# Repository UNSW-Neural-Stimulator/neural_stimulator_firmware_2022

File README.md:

# Neural Stimulator Firmware 2022

This is the repository for the Neural Stimulator Firmware team for 2022.

## Contents:

All of the work of the Firmware team for this year is divided up into two folders:
* The `/firmware` folder contains the actual firmware for the project
  * The `NSTIM` project in the `BLE_DAC` workspace contains the actual firmware for the neural stimulator.
* The `/other` folder contains all of the other code created by the team (i.e. weekly tasks)

## Making Changes:

If you wish to make any changes to the repo, please do the following: 
* Make a copy of the repository using `git clone <SSH or HTTPS>`
* Make a new branch for the repo:
  * On **GitHub**: Using the branches, enter your new branch name and click "create"
  * On **Local Terminal**: Enter into your terminal: `git checkout -b <new_branch_name>`
* Checkout your new branch in the terminal by entering `git fetch && git checkout <new_branch_name>`
* Regularly commit your changes by using `git add` and `git commit`
* When you wish to push your local branch changes to your remote branch, use `git push origin <new_branch_name>` 
* When you wish to merge your changes into the `master` branch, visit the branches page and select, "New pull request" [^1]

[^1]: It's not good practice to push anything directly to the `master` branch. By creating pull requests, it allows for somebody else to review your code and also makes it easier to isolate errors (since pull requests often contain multiple commits)

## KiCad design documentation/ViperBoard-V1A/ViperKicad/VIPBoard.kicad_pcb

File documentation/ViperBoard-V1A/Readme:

# Readme

  * Manufacture:
    Contains files sent to JLCPCB for manufacture and assembly. This includes BOM and pick and place position file. Solder mask contains exclusions for parts unable to be sourced from manufacturer.
  * ViperKicad:
    The KiCad 6.0 project. Includes schematic and PCB layout.
  * Documents:
    interactive_pcb.html: Very useful to view where things are on the PCB. Provides interactive inspection of component values and nets.
    VIPBoard-schematic.pdf: Circuit schematic of the stimulator. First sheet contains hierarchy. Following pages contain subcircuits e.g. MCU and current source.
    VIPBoard_3D.step: 3D model of the board and components. 
                      **For reference and graphical illustration ONLY.** 
                      Should not be considered dimensionally accurate as components are not sourced from datasheets.

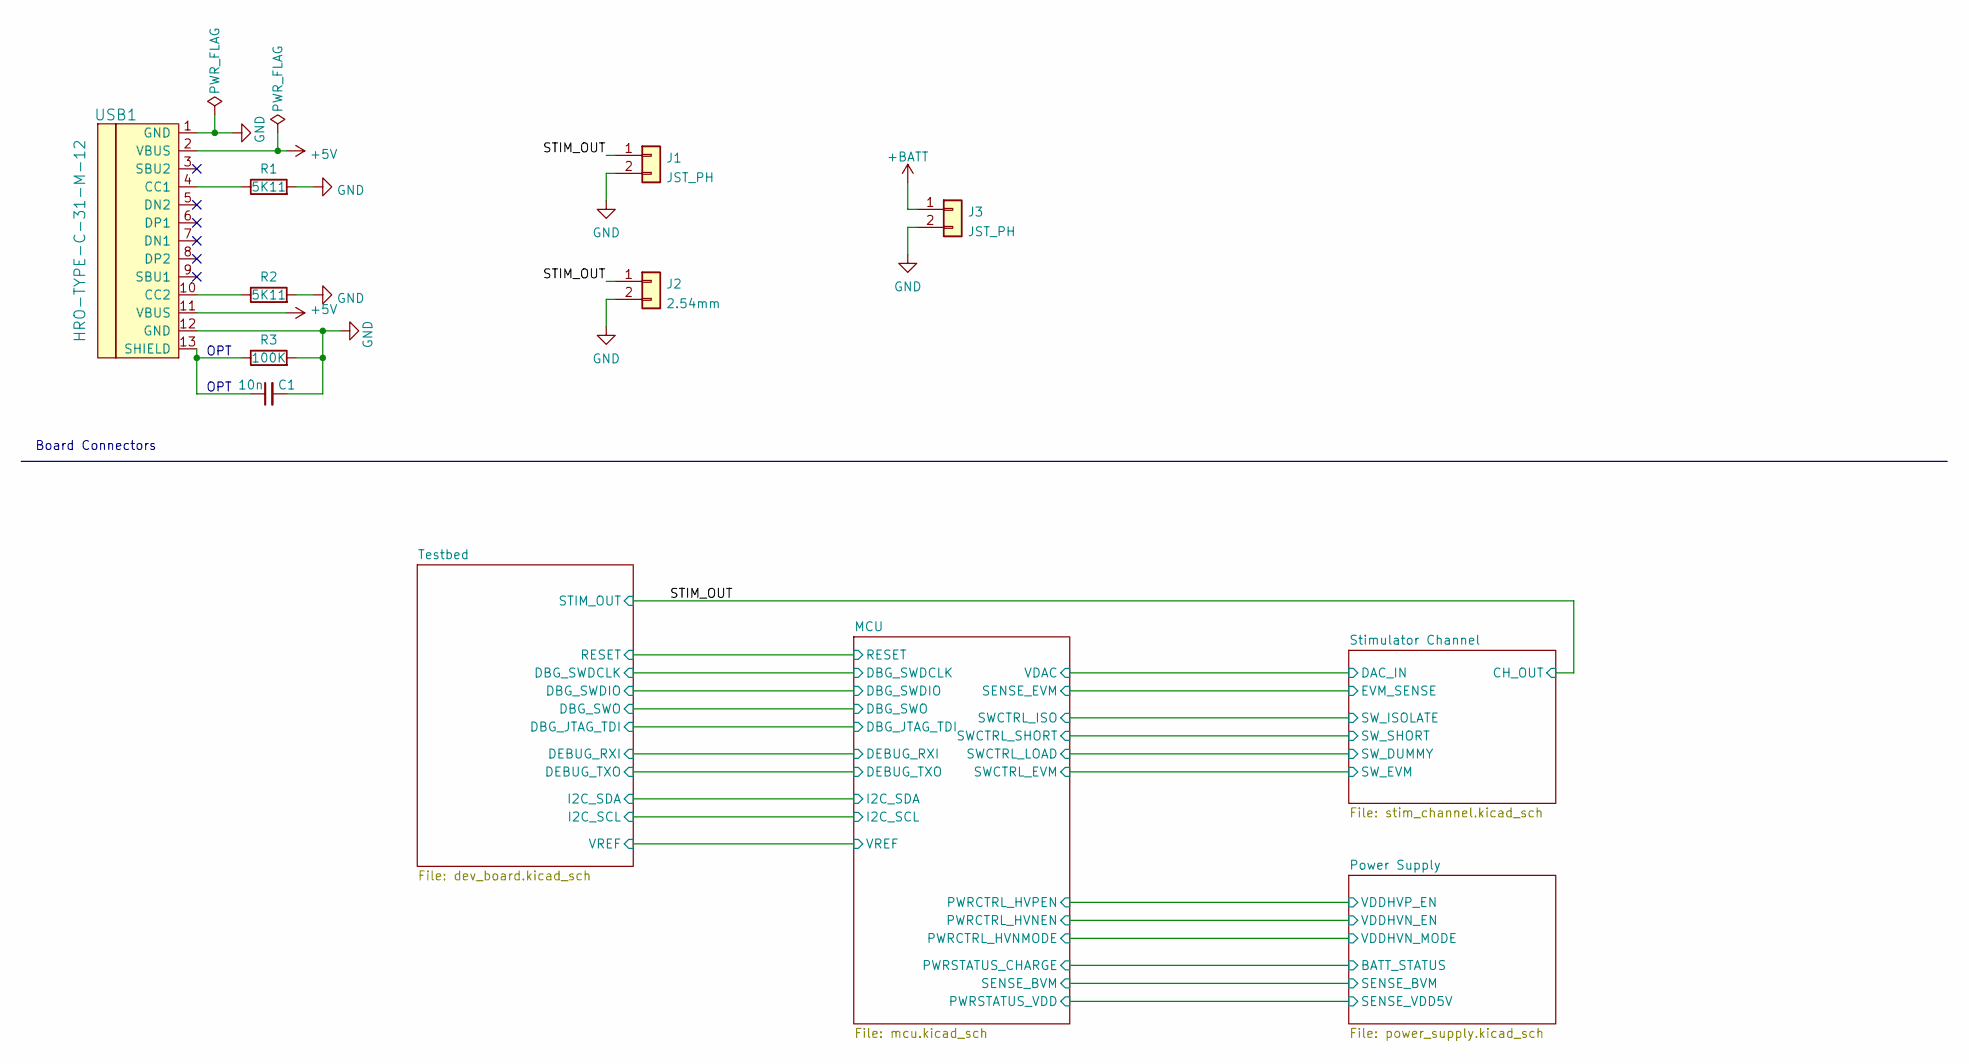
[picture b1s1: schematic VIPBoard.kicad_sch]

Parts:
C1: 10n; C_0402_1005Metric; LCSC C15195
J1, J3: JST_PH; JST_PH_S2B-PH-K_1x02_P2.00mm_Horizontal; LCSC C16965
J2: 2.54mm; PinHeader_1x02_P2.54mm_Vertical
R1, R2: 5K11; R_0402_1005Metric; LCSC C25905
R3: 100K; R_0402_1005Metric; LCSC C25741
USB1: HRO-TYPE-C-31-M-12; HRO-TYPE-C-31-M-12-HandSoldering; LCSC C167321

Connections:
+5V: USB1.2 (VBUS), USB1.11 (VBUS); also elsewhere on the board
+BATT: J3.1; also elsewhere on the board
/STIM_OUT: J1.1, J2.1; also elsewhere on the board
GND: C1.2, J1.2, J2.2, J3.2, R1.2, R2.2, R3.2, USB1.1 (GND), USB1.12 (GND); also elsewhere on the board
unnamed: C1.1, R3.1, USB1.13 (SHIELD)
unnamed: R1.1, USB1.4 (CC1)
unnamed: R2.1, USB1.10 (CC2)

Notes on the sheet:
Board Connectors
OPT

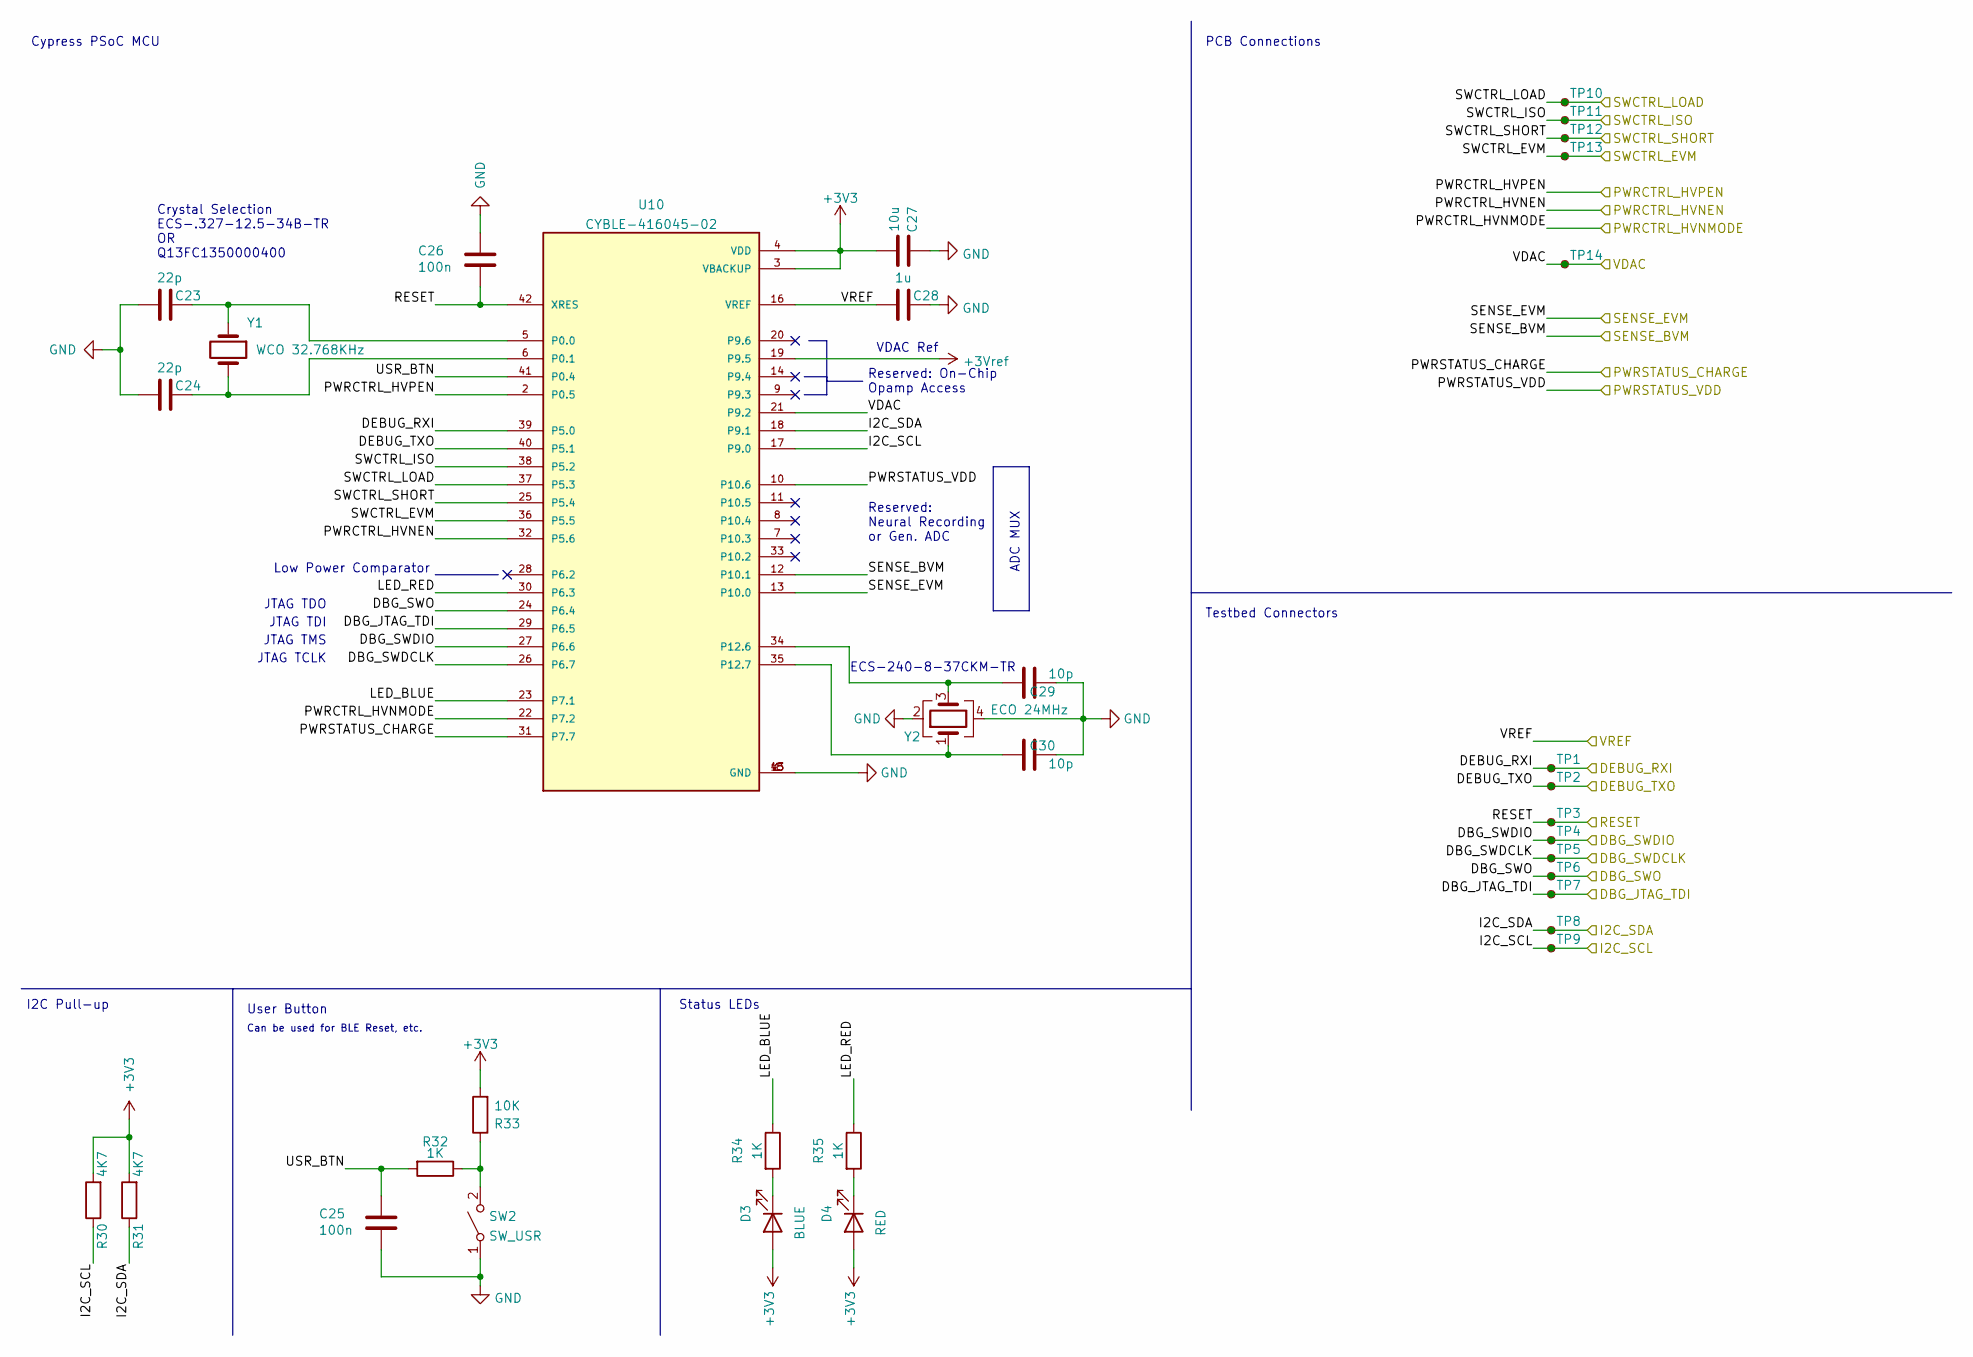
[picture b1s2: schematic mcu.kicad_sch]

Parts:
C23, C24: 22p; C_0402_1005Metric; LCSC C1555
C25, C26: 100n; C_0402_1005Metric; LCSC C307331
C27: 10u; C_0805_2012Metric; LCSC C440198
C28: 1u; C_0805_2012Metric; LCSC C28323
C29, C30: 10p; C_0402_1005Metric; LCSC C32949
D3: BLUE; LED_0603_1608Metric; LCSC C72041
D4: RED; LED_0603_1608Metric; LCSC C2286
R30, R31: 4K7; R_0402_1005Metric; LCSC C25900
R32, R34, R35: 1K; R_0402_1005Metric; LCSC C11702
R33: 10K; R_0402_1005Metric; LCSC C25744
SW2: SW_USR; SW_SPST_TL3342; LCSC C318884
TP1, TP2, TP3, TP4, TP5, TP6, TP7, TP8, TP9, TP10, TP11, TP12, TP13, TP14: TestPoint_Small; TestPoint_Pad_D1.0mm
U10: CYBLE-416045-02; XCVR_CYBLE-416045-02; PARTREV A
Y1: WCO 32.768KHz; Crystal_SMD_3215-2Pin_3.2x1.5mm; LCSC C32346
Y2: ECO 24MHz; Crystal_SMD_2016-4Pin_2.0x1.6mm

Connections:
+3V3: C27.2, D3.2 (A), D4.2 (A), R30.2, R31.2, R33.2, U10.3 (VBACKUP), U10.4 (VDD); also elsewhere on the board
+3Vref: U10.19 (P9.5); also elsewhere on the board
/MCU/DBG_JTAG_TDI: TP7.1, U10.29 (P6.5); also elsewhere on the board
/MCU/DBG_SWDCLK: TP5.1, U10.26 (P6.7); also elsewhere on the board
/MCU/DBG_SWDIO: TP4.1, U10.27 (P6.6); also elsewhere on the board
/MCU/DBG_SWO: TP6.1, U10.24 (P6.4); also elsewhere on the board
/MCU/DEBUG_RXI: TP1.1, U10.39 (P5.0); also elsewhere on the board
/MCU/DEBUG_TXO: TP2.1, U10.40 (P5.1); also elsewhere on the board
/MCU/I2C_SCL: R30.1, TP9.1, U10.17 (P9.0); also elsewhere on the board
/MCU/I2C_SDA: R31.1, TP8.1, U10.18 (P9.1); also elsewhere on the board
/MCU/LED_BLUE: R34.1, U10.23 (P7.1)
/MCU/LED_RED: R35.1, U10.30 (P6.3)
/MCU/PWRCTRL_HVNEN: U10.32 (P5.6); also elsewhere on the board
/MCU/PWRCTRL_HVNMODE: U10.22 (P7.2); also elsewhere on the board
/MCU/PWRCTRL_HVPEN: U10.2 (P0.5); also elsewhere on the board
/MCU/PWRSTATUS_CHARGE: U10.31 (P7.7); also elsewhere on the board
/MCU/PWRSTATUS_VDD: U10.10 (P10.6); also elsewhere on the board
/MCU/RESET: C26.2, TP3.1, U10.42 (XRES); also elsewhere on the board
/MCU/SENSE_BVM: U10.12 (P10.1); also elsewhere on the board
/MCU/SENSE_EVM: U10.13 (P10.0); also elsewhere on the board
/MCU/SWCTRL_EVM: TP13.1, U10.36 (P5.5); also elsewhere on the board
/MCU/SWCTRL_ISO: TP11.1, U10.38 (P5.2); also elsewhere on the board
/MCU/SWCTRL_LOAD: TP10.1, U10.37 (P5.3); also elsewhere on the board
/MCU/SWCTRL_SHORT: TP12.1, U10.25 (P5.4); also elsewhere on the board
/MCU/USR_BTN: C25.1, R32.2, U10.41 (P0.4)
/MCU/VDAC: TP14.1, U10.21 (P9.2); also elsewhere on the board
/MCU/VREF: C28.2, U10.16 (VREF); also elsewhere on the board
GND: C23.2, C24.2, C25.2, C26.1, C27.1, C28.1, C29.2, C30.2, SW2.1 (A), U10.1 (GND), U10.15 (GND), U10.43 (GND), Y2.2, Y2.4; also elsewhere on the board
unnamed: C23.1, U10.5 (P0.0), Y1.1
unnamed: C24.1, U10.6 (P0.1), Y1.2
unnamed: C29.1, U10.34 (P12.6), Y2.3
unnamed: C30.1, U10.35 (P12.7), Y2.1
unnamed: D3.1 (K), R34.2
unnamed: D4.1 (K), R35.2
unnamed: R32.1, R33.1, SW2.2 (B)

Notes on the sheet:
Low Power Comparator
JTAG TCLK
Reserved: On-Chip Opamp Access
Can be used for BLE Reset, etc.
Reserved: Neural Recording or Gen. ADC
Crystal Selection ECS-.327-12.5-34B-TR OR Q13FC1350000400
Testbed Connectors
JTAG TDO
JTAG TMS
ECS-240-8-37CKM-TR
I2C Pull-up
PCB Connections
Cypress PSoC MCU
VDAC Ref
JTAG TDI
ADC MUX
User Button
Status LEDs

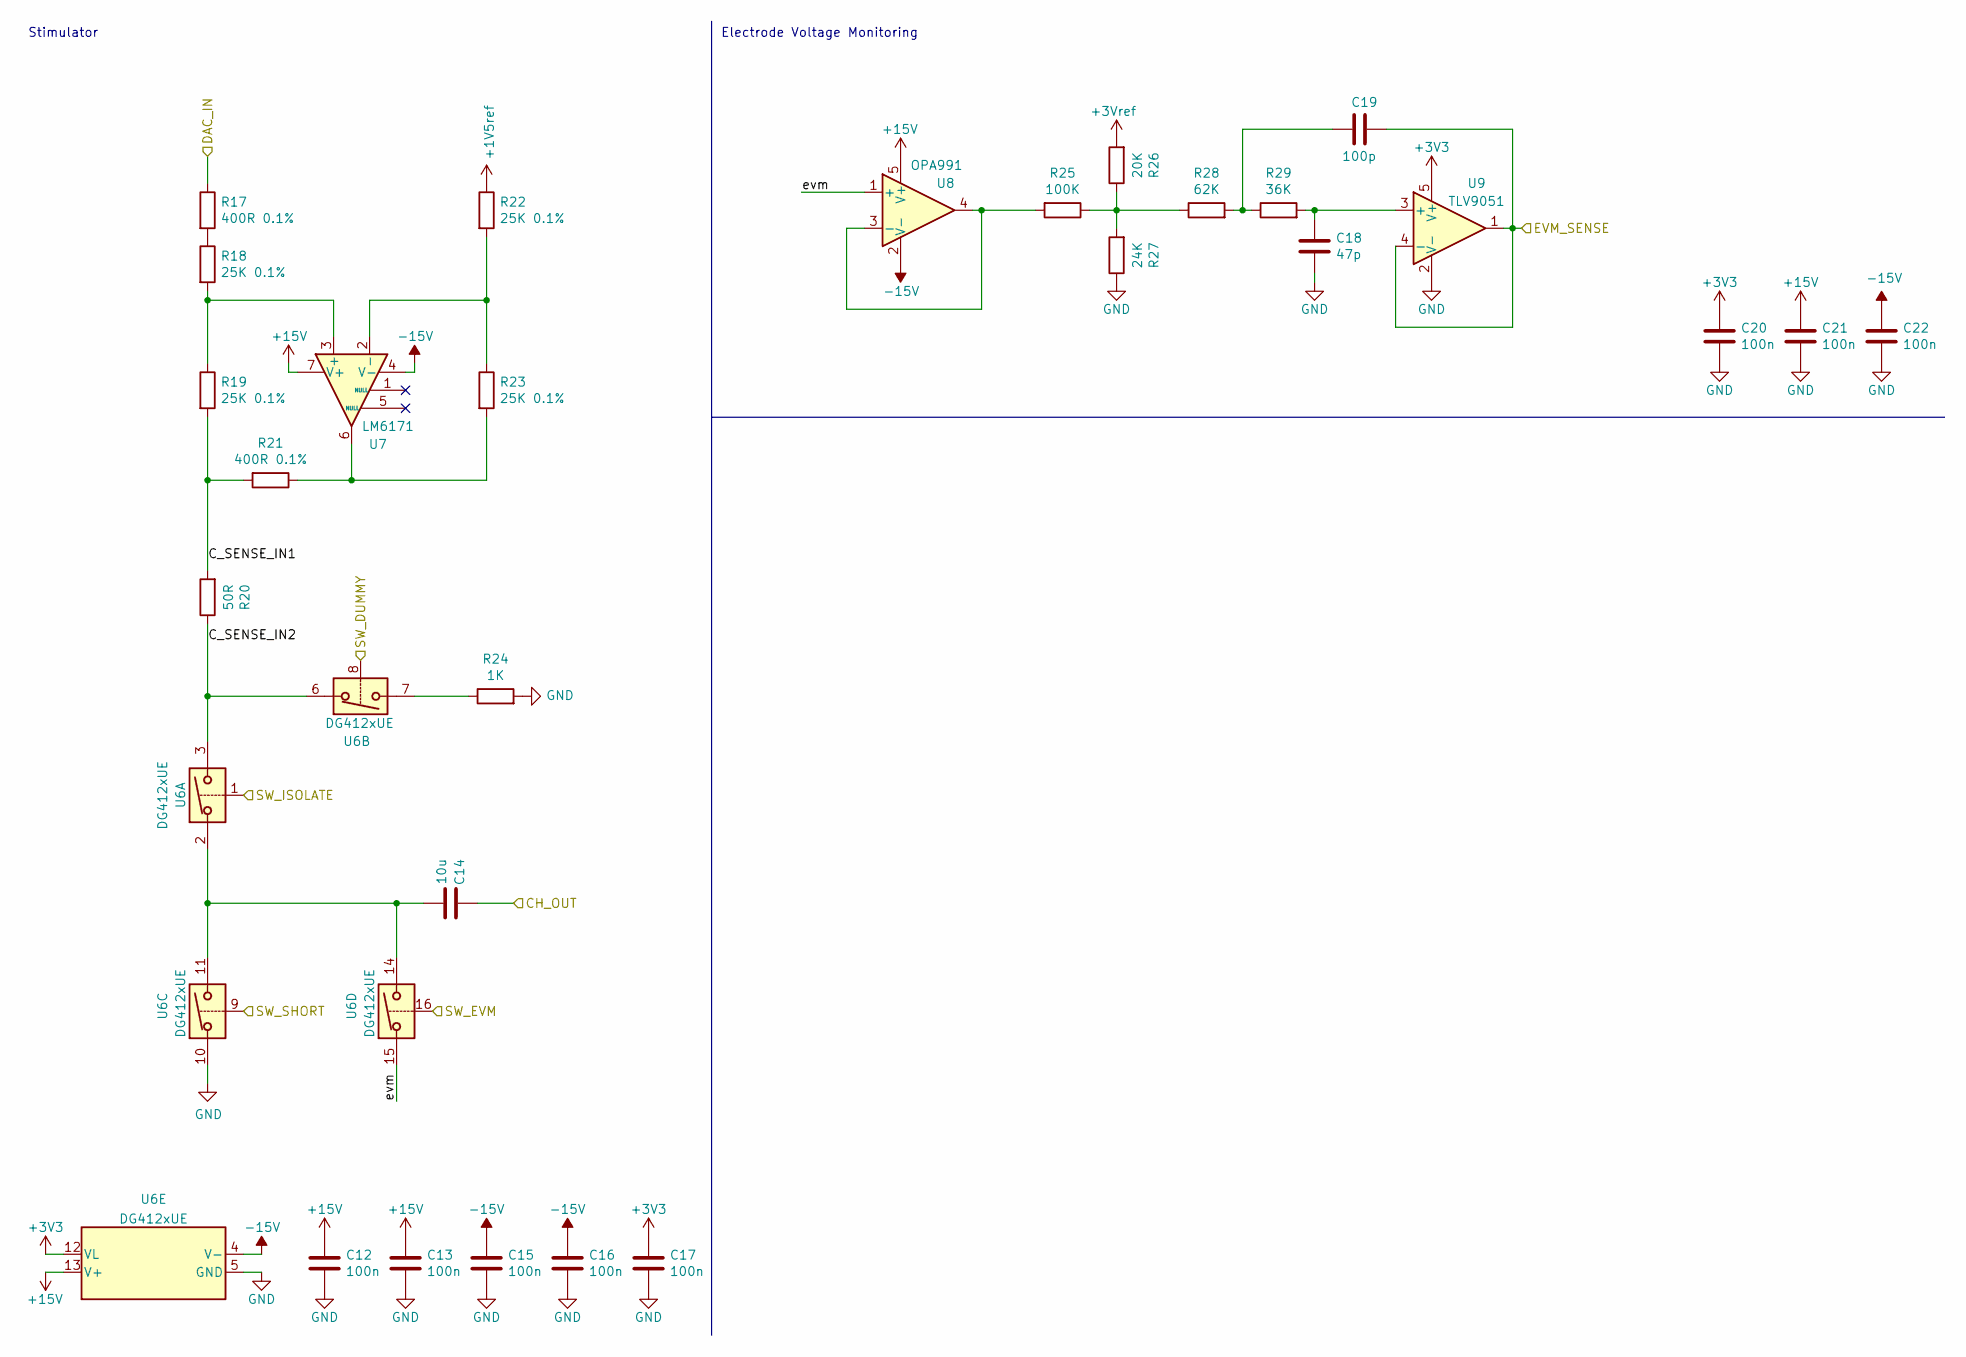
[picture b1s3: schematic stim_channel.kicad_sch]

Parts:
C12, C13, C15, C16, C17, C20, C21, C22: 100n; C_0402_1005Metric; LCSC C307331
C14: 10u; C_0805_2012Metric; LCSC C440198
C18: 47p; C_0402_1005Metric; LCSC C1567
C19: 100p; C_0402_1005Metric; LCSC C1546
R17, R21: 400R 0.1%; R_0402_1005Metric; LCSC C317913
R18, R19, R22, R23: 25K 0.1%; R_0402_1005Metric; LCSC C136978
R20: 50R; R_0402_1005Metric; LCSC C25120
R24: 1K; R_0402_1005Metric; LCSC C11702
R25: 100K; R_0402_1005Metric; LCSC C25741
R26: 20K; R_0402_1005Metric; LCSC C25765
R27: 24K; R_0402_1005Metric; LCSC C25769
R28: 62K; R_0603_1608Metric; LCSC C23221
R29: 36K; R_0603_1608Metric; LCSC C23147
U6: DG412xUE; TSSOP-16_4.4x5mm_P0.65mm
U7: LM6171; SOIC-8_3.9x4.9mm_P1.27mm
U8: OPA991; SOT-353_SC-70-5
U9: TLV9051; SOT-23-5

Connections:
+1V5ref: R22.1; also elsewhere on the board
+3V3: C17.1, C20.1, U6.12 (VL), U9.5 (V+); also elsewhere on the board
+3Vref: R26.2; also elsewhere on the board
+15V: C12.1, C13.1, C21.1, U6.13 (V+), U7.7 (V+), U8.5 (V+); also elsewhere on the board
-15V: C15.1, C16.1, C22.1, U6.4 (V-), U7.4 (V-), U8.2 (V-); also elsewhere on the board
/MCU/SENSE_EVM: C19.1, U9.1, U9.4 (-); also elsewhere on the board
/MCU/SWCTRL_EVM: U6.16; also elsewhere on the board
/MCU/SWCTRL_ISO: U6.1; also elsewhere on the board
/MCU/SWCTRL_LOAD: U6.8; also elsewhere on the board
/MCU/SWCTRL_SHORT: U6.9; also elsewhere on the board
/MCU/VDAC: R17.1; also elsewhere on the board
/STIM_OUT: C14.1; also elsewhere on the board
/Stimulator Channel/C_SENSE_IN1: R19.2, R20.2, R21.2
/Stimulator Channel/C_SENSE_IN2: R20.1, U6.3, U6.6
/Stimulator Channel/evm: U6.15, U8.1 (+)
GND: C12.2, C13.2, C15.2, C16.2, C17.2, C18.2, C20.2, C21.2, C22.2, R24.2, R27.1, U6.5 (GND), U6.10, U9.2 (V-); also elsewhere on the board
unnamed: C14.2, U6.2, U6.11, U6.14
unnamed: C18.1, R29.2, U9.3 (+)
unnamed: C19.2, R28.2, R29.1
unnamed: R17.2, R18.1
unnamed: R18.2, R19.1, U7.3 (+)
unnamed: R21.1, R23.2, U7.6
unnamed: R22.2, R23.1, U7.2 (-)
unnamed: R24.1, U6.7
unnamed: R25.1, R26.1, R27.2, R28.1
unnamed: R25.2, U8.3 (-), U8.4

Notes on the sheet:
Electrode Voltage Monitoring
Stimulator

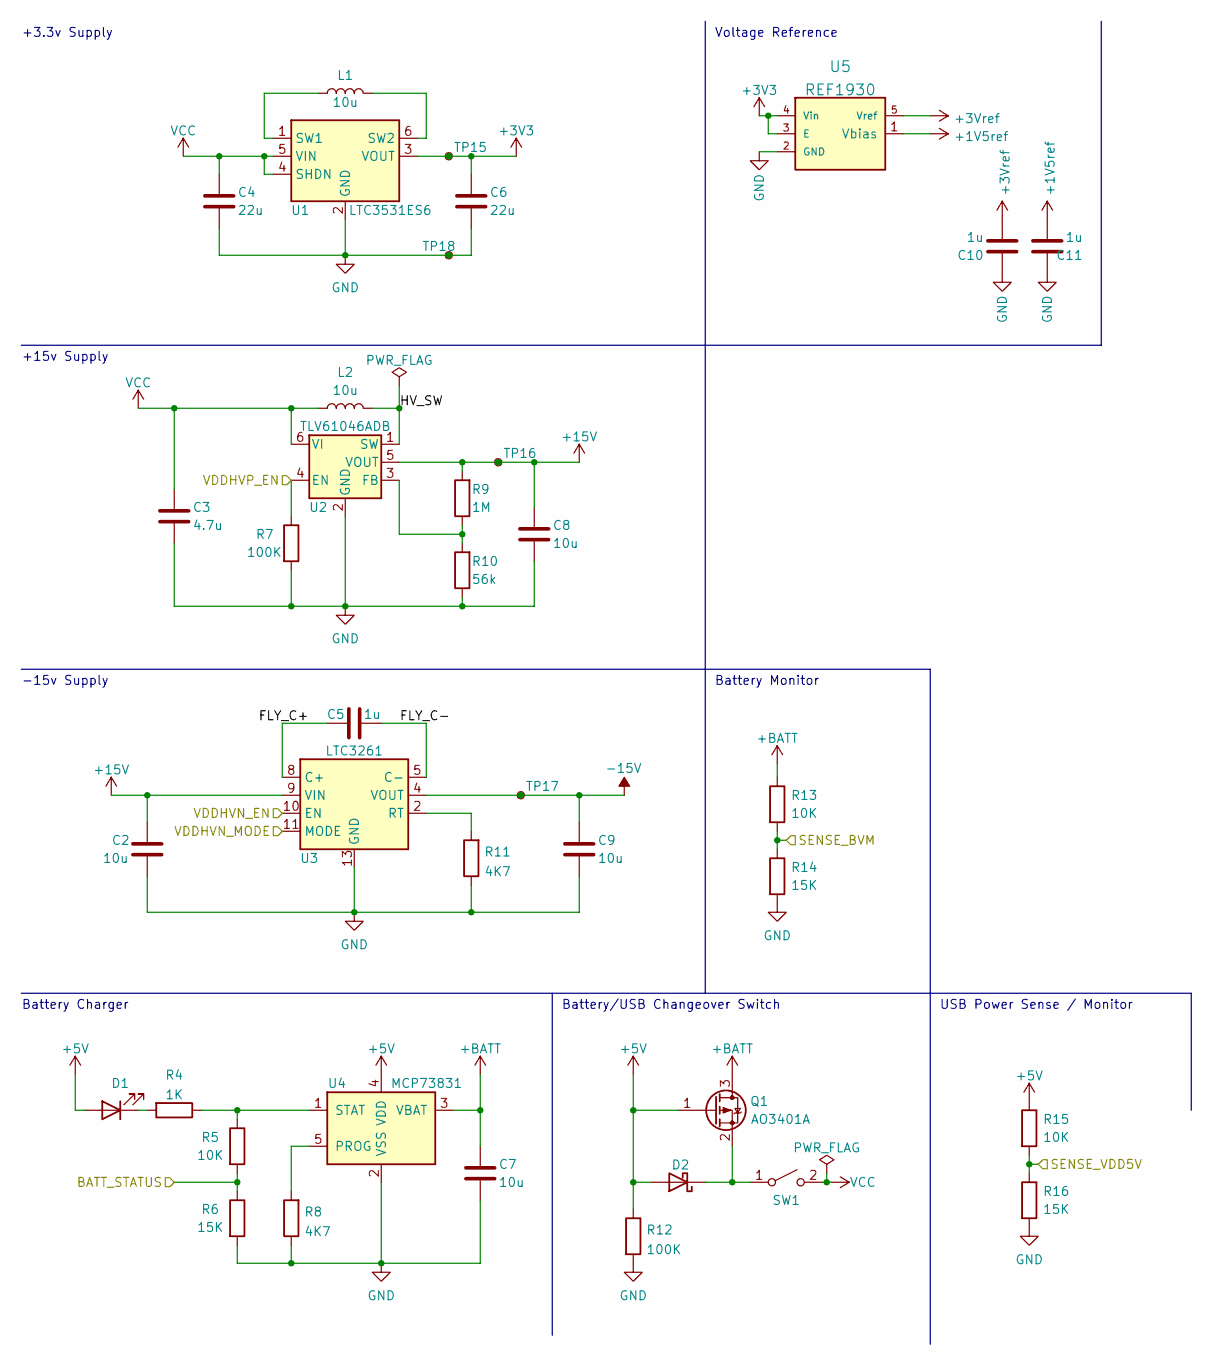
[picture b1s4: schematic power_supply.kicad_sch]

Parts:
C2, C7, C8, C9: 10u; C_0805_2012Metric; LCSC C440198
C3: 4.7u; C_0603_1608Metric; LCSC C19666
C4, C6: 22u; C_0805_2012Metric; LCSC C45783
C5, C10, C11: 1u; C_0805_2012Metric; LCSC C28323
D1: RED; LED_0603_1608Metric; LCSC C2286
D2: D_Schottky; D_SOD-323; LCSC C191023
L1, L2: 10u; 4.4x4.2x2mm Power Inductor; LCSC C177242
Q1: AO3401A; SOT-23; LCSC C15127
R4: 1K; R_0402_1005Metric; LCSC C11702
R5, R13, R15: 10K; R_0402_1005Metric; LCSC C25744
R6, R14, R16: 15K; R_0402_1005Metric; LCSC C25756
R7, R12: 100K; R_0402_1005Metric; LCSC C25741
R8, R11: 4K7; R_0402_1005Metric; LCSC C25900
R9: 1M; R_0402_1005Metric; LCSC C26083
R10: 56k; R_0402_1005Metric; LCSC C25796
SW1: SW_SPST; SW_SPDT_PCM12; LCSC C431540
TP15, TP16, TP17, TP18: TestPoint_Small; TestPoint_Pad_D1.0mm
U1: LTC3531ES6; SOT-23-6
U2: TLV61046ADB; SOT-23-6
U3: LTC3261; MSOP-12-1EP_3x4mm_P0.65mm_EP1.65x2.85mm_ThermalVias
U4: MCP73831; SOT-23-5
U5: REF1930; SOT-23-5_HandSoldering

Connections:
+1V5ref: C11.2, U5.1 (Vbias); also elsewhere on the board
+3V3: C6.1, TP15.1, U1.3 (VOUT), U5.3 (E), U5.4 (Vin); also elsewhere on the board
+3Vref: C10.2, U5.5 (Vref); also elsewhere on the board
+5V: D1.2 (A), D2.2 (A), Q1.1 (G), R12.1, R15.1, U4.4 (VDD); also elsewhere on the board
+15V: C2.1, C8.1, R9.2, TP16.1, U2.5 (VOUT), U3.9 (VIN); also elsewhere on the board
+BATT: C7.1, Q1.3 (D), R13.1, U4.3 (VBAT); also elsewhere on the board
-15V: C9.1, TP17.1, U3.4 (VOUT); also elsewhere on the board
/MCU/PWRCTRL_HVNEN: U3.10 (EN); also elsewhere on the board
/MCU/PWRCTRL_HVNMODE: U3.11 (MODE); also elsewhere on the board
/MCU/PWRCTRL_HVPEN: R7.1, U2.4 (EN); also elsewhere on the board
/MCU/PWRSTATUS_CHARGE: R5.2, R6.1; also elsewhere on the board
/MCU/PWRSTATUS_VDD: R15.2, R16.1; also elsewhere on the board
/MCU/SENSE_BVM: R13.2, R14.1; also elsewhere on the board
/Power Supply/FLY_C+: C5.1, U3.7 (C+), U3.8 (C+)
/Power Supply/FLY_C-: C5.2, U3.5 (C-), U3.6 (C-)
/Power Supply/HV_SW: L2.2, U2.1 (SW)
GND: C2.2, C3.2, C4.2, C6.2, C7.2, C8.2, C9.2, C10.1, C11.1, R6.2, R7.2, R8.1, R10.1, R11.1, R12.2, R14.2, R16.2, TP18.1, U1.2 (GND), U2.2 (GND), U3.13 (GND), U4.2 (VSS), U5.2 (GND); also elsewhere on the board
unnamed: D1.1 (K), R4.2
unnamed: D2.1 (K), Q1.2 (S), SW1.1 (A)
unnamed: L1.1, U1.1 (SW1)
unnamed: L1.2, U1.6 (SW2)
unnamed: R4.1, R5.1, U4.1 (STAT)
unnamed: R8.2, U4.5 (PROG)
unnamed: R9.1, R10.2, U2.3 (FB)
unnamed: R11.2, U3.2 (RT)
VCC: C3.1, C4.1, L2.1, SW1.2 (B), U1.4 (SHDN), U1.5 (VIN), U2.6 (VI)

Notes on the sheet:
+15v Supply
Battery Monitor
USB Power Sense / Monitor
Battery/USB Changeover Switch
Battery Charger
-15v Supply
Voltage Reference
+3.3v Supply

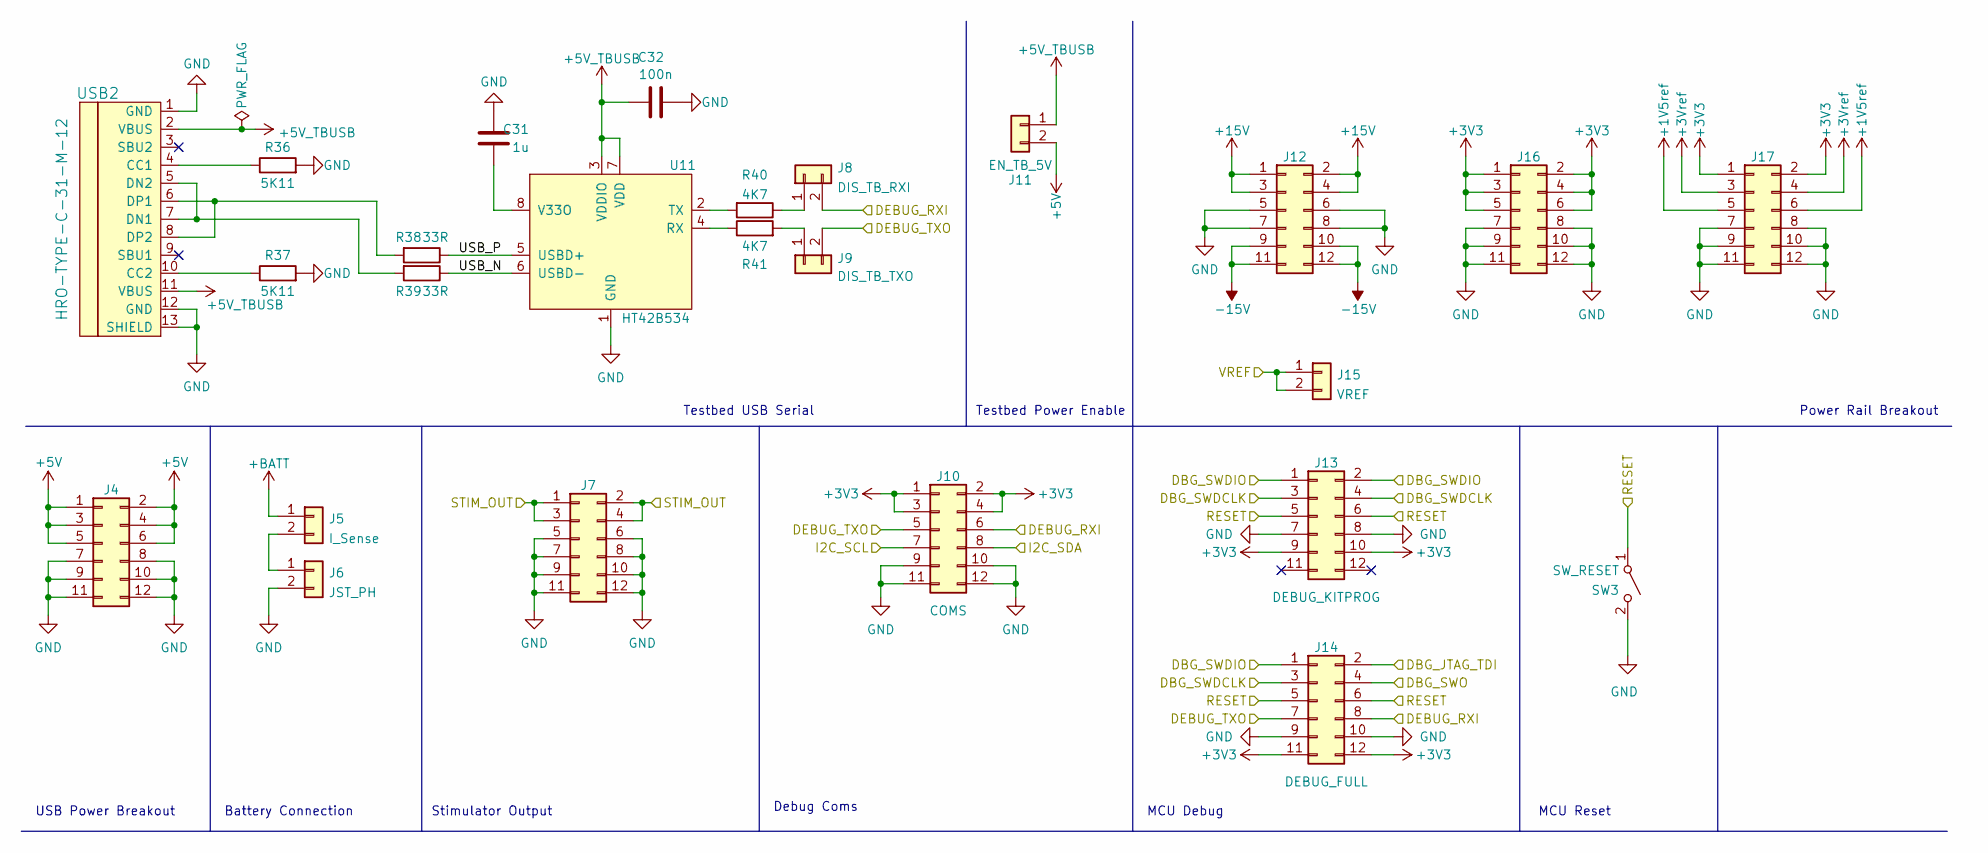
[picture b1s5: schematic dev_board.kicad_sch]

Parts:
C31: 1u; C_0805_2012Metric; LCSC C28323
C32: 100n; C_0402_1005Metric; LCSC C307331
J4, J7, J12, J16, J17: Conn_02x06_Odd_Even; PinHeader_2x06_P2.54mm_Vertical; LCSC C124388
J5: I_Sense; PinHeader_1x02_P2.54mm_Vertical; LCSC C492401
J6: JST_PH; JST_PH_S2B-PH-K_1x02_P2.00mm_Horizontal; LCSC C16965
J8: DIS_TB_RXI; PinHeader_1x02_P2.54mm_Vertical; LCSC C492401
J9: DIS_TB_TXO; PinHeader_1x02_P2.54mm_Vertical; LCSC C492401
J10: COMS; PinHeader_2x06_P2.54mm_Vertical; LCSC C124388
J11: EN_TB_5V; PinHeader_1x02_P2.54mm_Vertical; LCSC C492401
J13: DEBUG_KITPROG; PinHeader_2x06_P2.54mm_Vertical; LCSC C124388
J14: DEBUG_FULL; PinHeader_2x06_P2.54mm_Vertical; LCSC C124388
J15: VREF; PinHeader_1x02_P2.54mm_Vertical; LCSC C492401
R36, R37: 5K11; R_0402_1005Metric; LCSC C25905
R38, R39: 33R; R_0402_1005Metric; LCSC C25105
R40, R41: 4K7; R_0402_1005Metric; LCSC C25900
SW3: SW_RESET; SW_SPST_TL3342; LCSC C318884
U11: HT42B534; SOIC-8_3.9x4.9mm_P1.27mm
USB2: HRO-TYPE-C-31-M-12; HRO-TYPE-C-31-M-12-HandSoldering; LCSC C167321

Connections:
+1V5ref: J17.5, J17.6; also elsewhere on the board
+3V3: J10.1, J10.2, J10.3, J10.4, J13.9, J13.10, J14.11, J14.12, J16.1, J16.2, J16.3, J16.4, J16.5, J16.6, J17.1, J17.2; also elsewhere on the board
+3Vref: J17.3, J17.4; also elsewhere on the board
+5V: J4.1, J4.2, J4.3, J4.4, J4.5, J4.6, J11.2; also elsewhere on the board
+5V_TBUSB: C32.1, J11.1, U11.3 (VDDIO), U11.7 (VDD), USB2.2 (VBUS), USB2.11 (VBUS)
+15V: J12.1, J12.2, J12.3, J12.4; also elsewhere on the board
+BATT: J5.1; also elsewhere on the board
-15V: J12.9, J12.10, J12.11, J12.12; also elsewhere on the board
/MCU/DBG_JTAG_TDI: J14.2; also elsewhere on the board
/MCU/DBG_SWDCLK: J13.3, J13.4, J14.3; also elsewhere on the board
/MCU/DBG_SWDIO: J13.1, J13.2, J14.1; also elsewhere on the board
/MCU/DBG_SWO: J14.4; also elsewhere on the board
/MCU/DEBUG_RXI: J8.2, J10.6, J14.8; also elsewhere on the board
/MCU/DEBUG_TXO: J9.2, J10.5, J14.7; also elsewhere on the board
/MCU/I2C_SCL: J10.7; also elsewhere on the board
/MCU/I2C_SDA: J10.8; also elsewhere on the board
/MCU/RESET: J13.5, J13.6, J14.5, J14.6, SW3.1 (A); also elsewhere on the board
/MCU/VREF: J15.1, J15.2; also elsewhere on the board
/STIM_OUT: J7.1, J7.2, J7.3, J7.4; also elsewhere on the board
/Testbed/USB_N: R39.1, U11.6 (USBD-)
/Testbed/USB_P: R38.1, U11.5 (USBD+)
GND: C31.2, C32.2, J4.7, J4.8, J4.9, J4.10, J4.11, J4.12, J6.2, J7.5, J7.6, J7.7, J7.8, J7.9, J7.10, J7.11, J7.12, J10.9, J10.10, J10.11, J10.12, J12.5, J12.6, J12.7, J12.8, J13.7, J13.8, J14.9, J14.10, J16.7, J16.8, J16.9, J16.10, J16.11, J16.12, J17.7, J17.8, J17.9, J17.10, J17.11, J17.12, R36.2, R37.2, SW3.2 (B), U11.1 (GND), USB2.1 (GND), USB2.12 (GND), USB2.13 (SHIELD); also elsewhere on the board
unnamed: C31.1, U11.8 (V33O)
unnamed: J5.2, J6.1
unnamed: J8.1, R40.1
unnamed: J9.1, R41.2
unnamed: R36.1, USB2.4 (CC1)
unnamed: R37.1, USB2.10 (CC2)
unnamed: R38.2, USB2.6 (DP1), USB2.8 (DP2)
unnamed: R39.2, USB2.5 (DN2), USB2.7 (DN1)
unnamed: R40.2, U11.2 (TX)
unnamed: R41.1, U11.4 (RX)

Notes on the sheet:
MCU Reset
USB Power Breakout
Power Rail Breakout
Stimulator Output
MCU Debug
Testbed Power Enable
Battery Connection
Testbed USB Serial
Debug Coms
